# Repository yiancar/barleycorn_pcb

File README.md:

Barleycorn
================

This ANSI/ISO 1800 F-row less keyboard kit is made using ONLY through hole components and inspired by the [Plaid](https://github.com/hsgw/plaid).

Atmega328p with VUSB on [QMK firmware](https://github.com/qmk/qmk_firmware).

To alter the pcb use KiCAD V5.0 or newer as it already contains most of the libraries. The additional libraries are provided.

License
===========

This project is licensed under the [Creative Commons Attribution-NonCommercial 4.0 International License](https://creativecommons.org/licenses/by-nc/4.0/).

If you have remixed, adapted or build upon this work and wish to remove the non-commercial clause for your own project please contact me at https://www.yiancar-designs.com. Your request is more than likely to be granted. The non-commercial part of the license is intended to avoid direct copies of the work to be sold for commercial gain by third parties.

The USB4085-GF-A footprint, symbol and 3D model are licensed under [Attribution-ShareAlike 4.0 International](https://creativecommons.org/licenses/by-sa/4.0/). Originally created by [SnapEDA](https://snapeda.com). The footprint has been modified to increase the hole size of the shield pads.

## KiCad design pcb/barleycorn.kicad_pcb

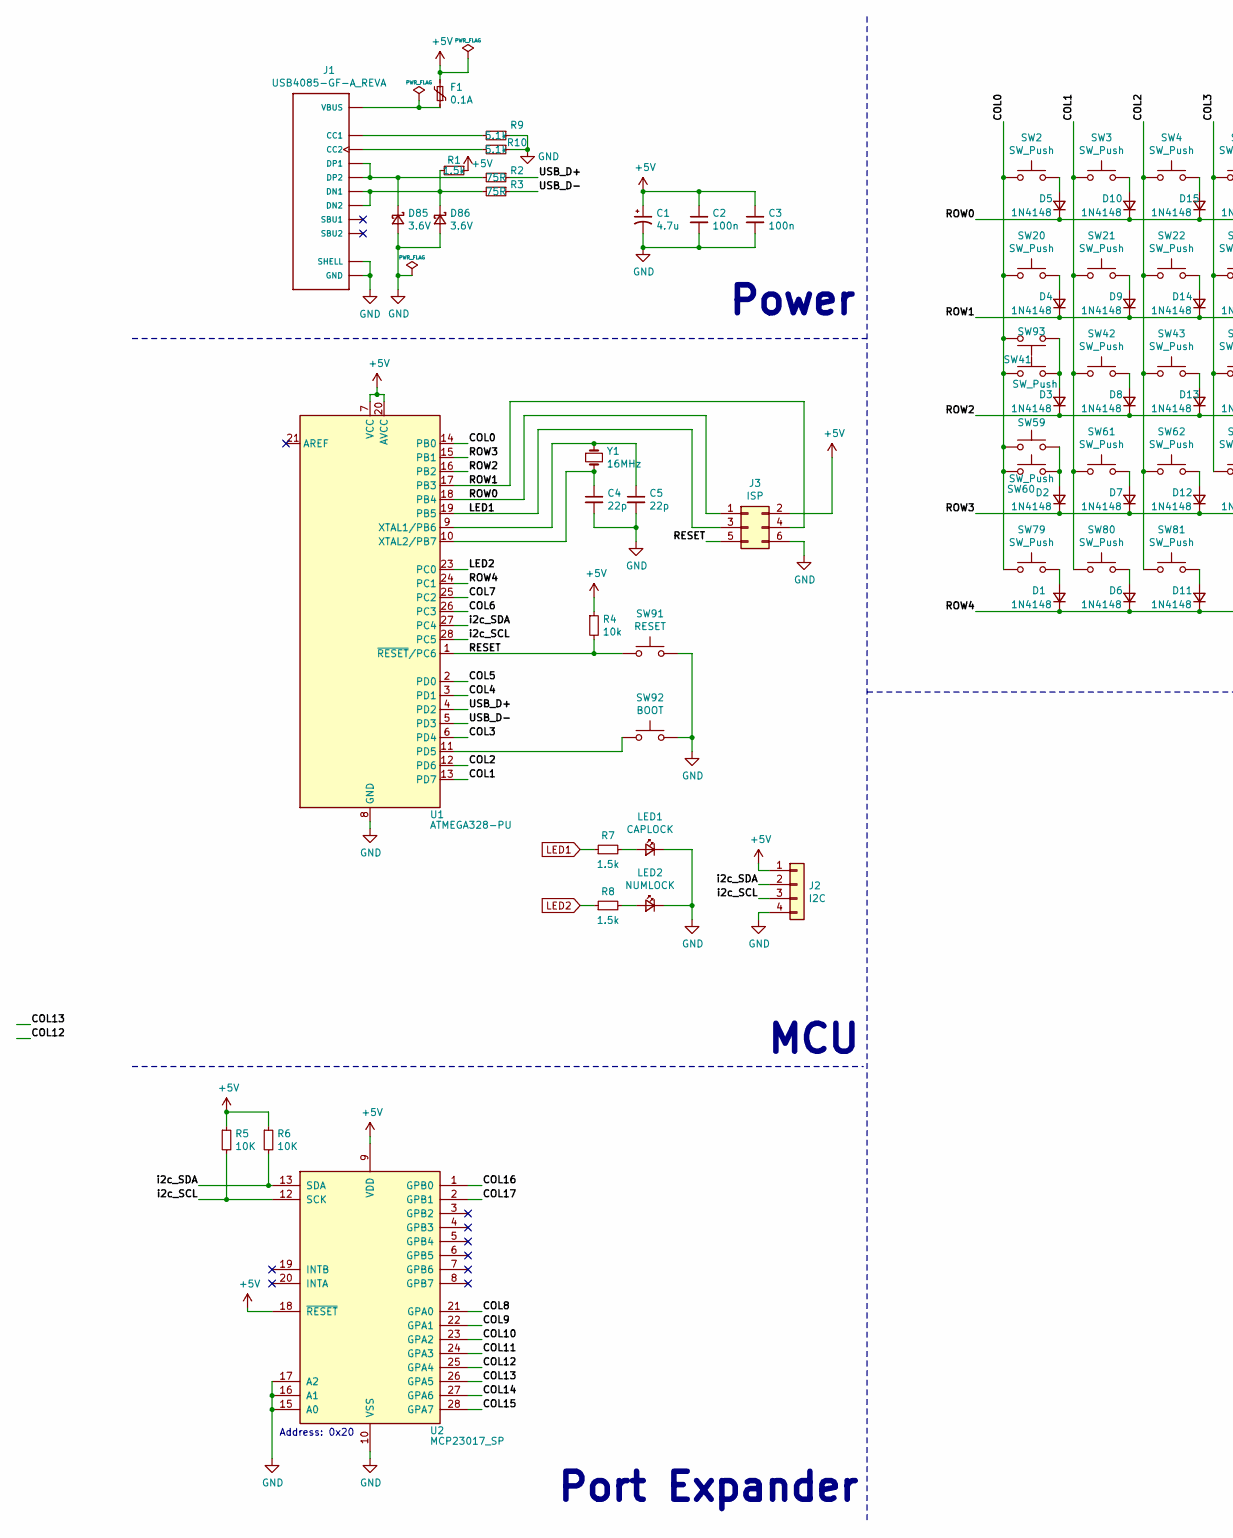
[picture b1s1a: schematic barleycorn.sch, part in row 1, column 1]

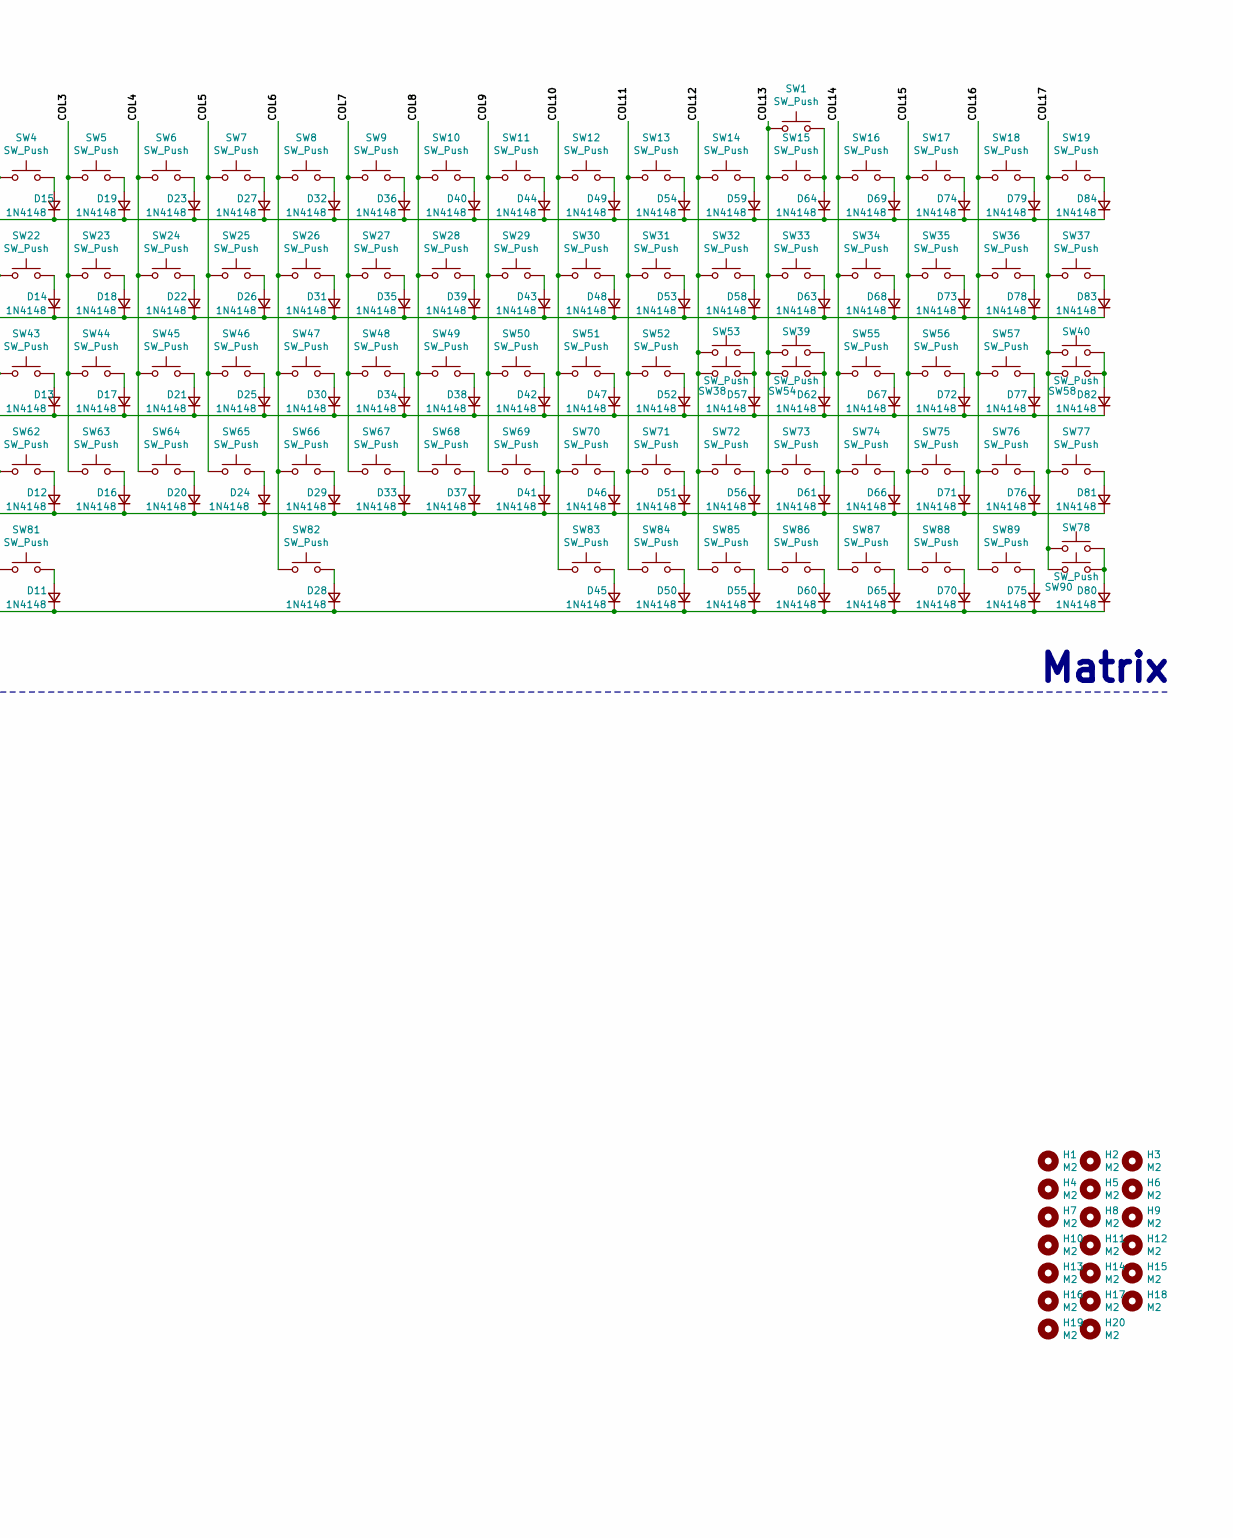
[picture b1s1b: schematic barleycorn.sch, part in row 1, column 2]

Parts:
C1: 4.7u; CP_Radial_D4.0mm_P1.50mm
C2, C3: 100n; C_Disc_D4.3mm_W1.9mm_P5.00mm
C4, C5: 22p; C_Disc_D4.3mm_W1.9mm_P5.00mm
D1, D2, D3, D4, D5, D6, D7, D8, D9, D10, D11, D12, D13, D14, D15, D16, D17, D18, D19, D20, D21, D22, D23, D24, D25, D26, D27, D28, D29, D30, D31, D32, D33, D34, D35, D36, D37, D38, D39, D40, D41, D42, D43, D44, D45, D46, D47, D48, D49, D50, D51, D52, D53, D54, D55, D56, D57, D58, D59, D60, D61, D62, D63, D64, D65, D66, D67, D68, D69, D70, D71, D72, D73, D74, D75, D76, D77, D78, D79, D80, D81, D82, D83, D84: 1N4148; D_DO-35_SOD27_P7.62mm_Horizontal
D85, D86: 3.6V; D_DO-35_SOD27_P7.62mm_Horizontal
F1: 0.1A; C_Disc_D5.0mm_W2.5mm_P5.00mm
H1, H2, H3, H4, H5, H6, H7, H8, H9, H10, H11, H12, H13, H14, H15, H16, H17, H18, H19, H20: M2; MountingHole_2.2mm_M2_DIN965_Pad
J1: USB4085-GF-A_REVA; GCT_USB4085-GF-A_REVA
J2: I2C; PinHeader_1x04_P2.54mm_Vertical
J3: ISP; PinHeader_2x03_P2.54mm_Vertical
LED1: CAPLOCK; LED_D3.0mm_Clear
LED2: NUMLOCK; LED_D3.0mm_Clear
R1, R7, R8: 1.5k; R_Axial_DIN0204_L3.6mm_D1.6mm_P5.08mm_Horizontal
R2, R3: 75R; R_Axial_DIN0204_L3.6mm_D1.6mm_P5.08mm_Horizontal
R4: 10k; R_Axial_DIN0204_L3.6mm_D1.6mm_P5.08mm_Horizontal
R5, R6: 10K; R_Axial_DIN0204_L3.6mm_D1.6mm_P5.08mm_Horizontal
R9, R10: 5.1k; R_Axial_DIN0204_L3.6mm_D1.6mm_P5.08mm_Horizontal
SW1, SW40, SW78: SW_Push; MX-2U-NoLED
SW2, SW3, SW4, SW5, SW6, SW7, SW8, SW9, SW10, SW11, SW12, SW13, SW14, SW15, SW16, SW17, SW18, SW19, SW21, SW22, SW23, SW24, SW25, SW26, SW27, SW28, SW29, SW30, SW31, SW32, SW33, SW34, SW35, SW36, SW37, SW38, SW42, SW43, SW44, SW45, SW46, SW47, SW48, SW49, SW50, SW51, SW52, SW55, SW56, SW57, SW58, SW61, SW62, SW63, SW64, SW65, SW66, SW67, SW68, SW69, SW70, SW71, SW73, SW74, SW75, SW76, SW77, SW85, SW86, SW87, SW88, SW89, SW90: SW_Push; MX-1U-NoLED
SW20, SW53, SW83, SW84: SW_Push; MX-1.5U-NoLED
SW39: SW_Push; MX-ISO-ReversedStabilizers
SW41, SW72: SW_Push; MX-1.75U-NoLED
SW54, SW60: SW_Push; MX-2.25U-NoLED
SW59, SW79, SW80, SW81, SW93: SW_Push; MX-1.25U-NoLED
SW82: SW_Push; MX-6.25U-ReversedStabilizers-NoLED
SW91: RESET; SW_PUSH_6mm
SW92: BOOT; SW_PUSH_6mm
U1: ATMEGA328-PU; DIP-28_W7.62mm
U2: MCP23017_SP; DIP-28_W7.62mm
Y1: 16MHz; Crystal_HC49-4H_Vertical

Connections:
+5V: C1.1, C2.1, C3.1, F1.2, J2.1, J3.2, R1.1, R4.1, R5.1, R6.1, U1.7 (VCC), U1.20 (AVCC), U2.9 (VDD), U2.18 (~RESET~)
/COL0: SW2.2, SW20.2, SW41.2, SW59.2, SW60.2, SW79.2, SW93.1, U1.14 (PB0)
/COL1: SW3.2, SW21.2, SW42.2, SW61.2, SW80.2, U1.13 (PD7)
/COL2: SW4.2, SW22.2, SW43.2, SW62.2, SW81.2, U1.12 (PD6)
/COL3: SW5.2, SW23.2, SW44.2, SW63.2, U1.6 (PD4)
/COL4: SW6.2, SW24.2, SW45.2, SW64.2, U1.3 (PD1)
/COL5: SW7.2, SW25.2, SW46.2, SW65.2, U1.2 (PD0)
/COL6: SW8.2, SW26.2, SW47.2, SW66.2, SW82.2, U1.26 (PC3)
/COL7: SW9.2, SW27.2, SW48.2, SW67.2, U1.25 (PC2)
/COL8: SW10.2, SW28.2, SW49.2, SW68.2, U2.21 (GPA0)
/COL9: SW11.2, SW29.2, SW50.2, SW69.2, U2.22 (GPA1)
/COL10: SW12.2, SW30.2, SW51.2, SW70.2, SW83.2, U2.23 (GPA2)
/COL11: SW13.2, SW31.2, SW52.2, SW71.2, SW84.2, U2.24 (GPA3)
/COL12: SW14.2, SW32.2, SW38.2, SW53.2, SW72.2, SW85.2, U2.25 (GPA4)
/COL13: SW1.2, SW15.2, SW33.2, SW39.2, SW54.2, SW73.2, SW86.2, U2.26 (GPA5)
/COL14: SW16.2, SW34.2, SW55.2, SW74.2, SW87.2, U2.27 (GPA6)
/COL15: SW17.2, SW35.2, SW56.2, SW75.2, SW88.2, U2.28 (GPA7)
/COL16: SW18.2, SW36.2, SW57.2, SW76.2, SW89.2, U2.1 (GPB0)
/COL17: SW19.2, SW37.2, SW40.2, SW58.2, SW77.2, SW78.2, SW90.2, U2.2 (GPB1)
/RESET: J3.5, R4.2, SW91.1, U1.1 (~RESET~/PC6)
/ROW0: D5.1 (K), D10.1 (K), D15.1 (K), D19.1 (K), D23.1 (K), D27.1 (K), D32.1 (K), D36.1 (K), D40.1 (K), D44.1 (K), D49.1 (K), D54.1 (K), D59.1 (K), D64.1 (K), D69.1 (K), D74.1 (K), D79.1 (K), D84.1 (K), J3.1, U1.18 (PB4)
/ROW1: D4.1 (K), D9.1 (K), D14.1 (K), D18.1 (K), D22.1 (K), D26.1 (K), D31.1 (K), D35.1 (K), D39.1 (K), D43.1 (K), D48.1 (K), D53.1 (K), D58.1 (K), D63.1 (K), D68.1 (K), D73.1 (K), D78.1 (K), D83.1 (K), J3.4, U1.17 (PB3)
/ROW2: D3.1 (K), D8.1 (K), D13.1 (K), D17.1 (K), D21.1 (K), D25.1 (K), D30.1 (K), D34.1 (K), D38.1 (K), D42.1 (K), D47.1 (K), D52.1 (K), D57.1 (K), D62.1 (K), D67.1 (K), D72.1 (K), D77.1 (K), D82.1 (K), U1.16 (PB2)
/ROW3: D2.1 (K), D7.1 (K), D12.1 (K), D16.1 (K), D20.1 (K), D24.1 (K), D29.1 (K), D33.1 (K), D37.1 (K), D41.1 (K), D46.1 (K), D51.1 (K), D56.1 (K), D61.1 (K), D66.1 (K), D71.1 (K), D76.1 (K), D81.1 (K), U1.15 (PB1)
/ROW4: D1.1 (K), D6.1 (K), D11.1 (K), D28.1 (K), D45.1 (K), D50.1 (K), D55.1 (K), D60.1 (K), D65.1 (K), D70.1 (K), D75.1 (K), D80.1 (K), U1.24 (PC1)
/USB_D+: R2.1, U1.4 (PD2)
/USB_D-: R3.1, U1.5 (PD3)
/i2c_SCL: J2.3, R5.2, U1.28 (PC5), U2.12 (SCK)
/i2c_SDA: J2.2, R6.2, U1.27 (PC4), U2.13 (SDA)
GND: C1.2, C2.2, C3.2, C4.2, C5.2, D85.2 (A), D86.2 (A), J1.A1 (GND), J1.A12 (GND), J1.B1 (GND), J1.B12 (GND), J1.P1 (SHELL), J1.P2 (SHELL), J1.P3 (SHELL), J1.P4 (SHELL), J2.4, J3.6, LED1.1 (K), LED2.1 (K), R9.1, R10.1, SW91.2, SW92.2, U1.8 (GND), U1.22 (GND), U2.10 (VSS), U2.15 (A0), U2.16 (A1), U2.17 (A2)
LED1: J3.3, R7.1, U1.19 (PB5)
LED2: R8.1, U1.23 (PC0)
unnamed: C4.1, U1.10 (XTAL2/PB7), Y1.2
unnamed: C5.1, U1.9 (XTAL1/PB6), Y1.1
unnamed: D1.2 (A), SW79.1
unnamed: D2.2 (A), SW59.1, SW60.1
unnamed: D3.2 (A), SW41.1, SW93.2
unnamed: D4.2 (A), SW20.1
unnamed: D5.2 (A), SW2.1
unnamed: D6.2 (A), SW80.1
unnamed: D7.2 (A), SW61.1
unnamed: D8.2 (A), SW42.1
unnamed: D9.2 (A), SW21.1
unnamed: D10.2 (A), SW3.1
unnamed: D11.2 (A), SW81.1
unnamed: D12.2 (A), SW62.1
unnamed: D13.2 (A), SW43.1
unnamed: D14.2 (A), SW22.1
unnamed: D15.2 (A), SW4.1
unnamed: D16.2 (A), SW63.1
unnamed: D17.2 (A), SW44.1
unnamed: D18.2 (A), SW23.1
unnamed: D19.2 (A), SW5.1
unnamed: D20.2 (A), SW64.1
unnamed: D21.2 (A), SW45.1
unnamed: D22.2 (A), SW24.1
unnamed: D23.2 (A), SW6.1
unnamed: D24.2 (A), SW65.1
unnamed: D25.2 (A), SW46.1
unnamed: D26.2 (A), SW25.1
unnamed: D27.2 (A), SW7.1
unnamed: D28.2 (A), SW82.1
unnamed: D29.2 (A), SW66.1
unnamed: D30.2 (A), SW47.1
unnamed: D31.2 (A), SW26.1
unnamed: D32.2 (A), SW8.1
unnamed: D33.2 (A), SW67.1
unnamed: D34.2 (A), SW48.1
unnamed: D35.2 (A), SW27.1
unnamed: D36.2 (A), SW9.1
unnamed: D37.2 (A), SW68.1
unnamed: D38.2 (A), SW49.1
unnamed: D39.2 (A), SW28.1
unnamed: D40.2 (A), SW10.1
unnamed: D41.2 (A), SW69.1
unnamed: D42.2 (A), SW50.1
unnamed: D43.2 (A), SW29.1
unnamed: D44.2 (A), SW11.1
unnamed: D45.2 (A), SW83.1
unnamed: D46.2 (A), SW70.1
unnamed: D47.2 (A), SW51.1
unnamed: D48.2 (A), SW30.1
unnamed: D49.2 (A), SW12.1
unnamed: D50.2 (A), SW84.1
unnamed: D51.2 (A), SW71.1
unnamed: D52.2 (A), SW52.1
unnamed: D53.2 (A), SW31.1
unnamed: D54.2 (A), SW13.1
unnamed: D55.2 (A), SW85.1
unnamed: D56.2 (A), SW72.1
unnamed: D57.2 (A), SW38.1, SW53.1
unnamed: D58.2 (A), SW32.1
unnamed: D59.2 (A), SW14.1
unnamed: D60.2 (A), SW86.1
unnamed: D61.2 (A), SW73.1
unnamed: D62.2 (A), SW39.1, SW54.1
unnamed: D63.2 (A), SW33.1
unnamed: D64.2 (A), SW1.1, SW15.1
unnamed: D65.2 (A), SW87.1
unnamed: D66.2 (A), SW74.1
unnamed: D67.2 (A), SW55.1
unnamed: D68.2 (A), SW34.1
unnamed: D69.2 (A), SW16.1
unnamed: D70.2 (A), SW88.1
unnamed: D71.2 (A), SW75.1
unnamed: D72.2 (A), SW56.1
unnamed: D73.2 (A), SW35.1
unnamed: D74.2 (A), SW17.1
unnamed: D75.2 (A), SW89.1
unnamed: D76.2 (A), SW76.1
unnamed: D77.2 (A), SW57.1
unnamed: D78.2 (A), SW36.1
unnamed: D79.2 (A), SW18.1
unnamed: D80.2 (A), SW78.1, SW90.1
unnamed: D81.2 (A), SW77.1
unnamed: D82.2 (A), SW40.1, SW58.1
unnamed: D83.2 (A), SW37.1
unnamed: D84.2 (A), SW19.1
unnamed: D85.1 (K), J1.A6 (DP1), J1.B6 (DP2), R2.2
unnamed: D86.1 (K), J1.A7 (DN1), J1.B7 (DN2), R1.2, R3.2
unnamed: F1.1, J1.A4 (VBUS), J1.A9 (VBUS), J1.B4 (VBUS), J1.B9 (VBUS)
unnamed: J1.A5 (CC1), R9.2
unnamed: J1.B5 (CC2), R10.2
unnamed: LED1.2 (A), R7.2
unnamed: LED2.2 (A), R8.2
unnamed: SW92.1, U1.11 (PD5)

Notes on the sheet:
Power
Matrix
MCU
Port Expander
Address: 0x20

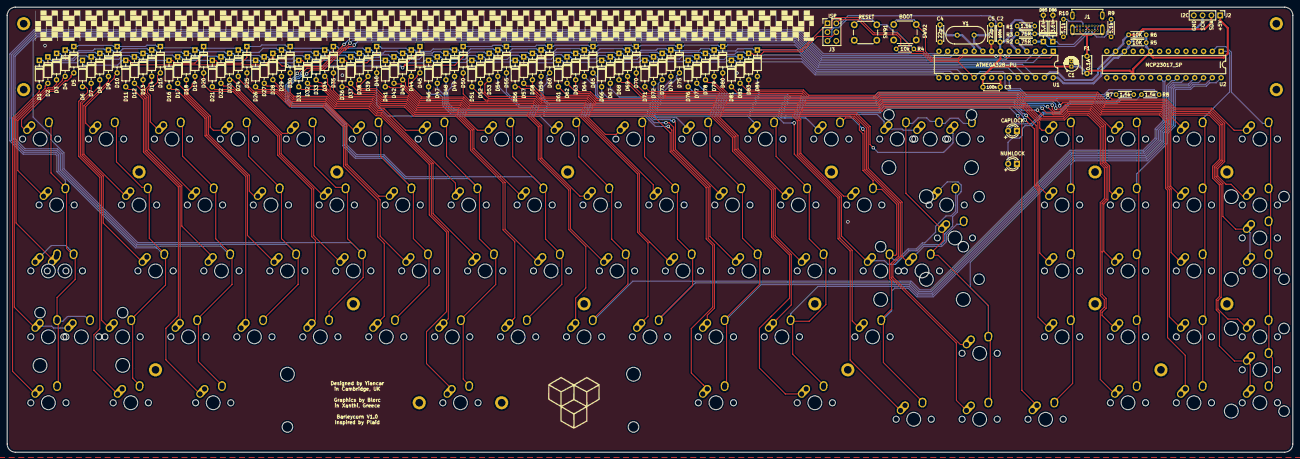
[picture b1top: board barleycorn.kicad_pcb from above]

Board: 2 copper layers, 371.5 x 128.6 mm, 224 parts (0 on the bottom side), 126 nets.

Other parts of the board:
Ref**: Val**; barleycorn_logo

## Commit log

2020-12-11 Printed Schematic

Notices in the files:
README.md:
cc-by-nc
